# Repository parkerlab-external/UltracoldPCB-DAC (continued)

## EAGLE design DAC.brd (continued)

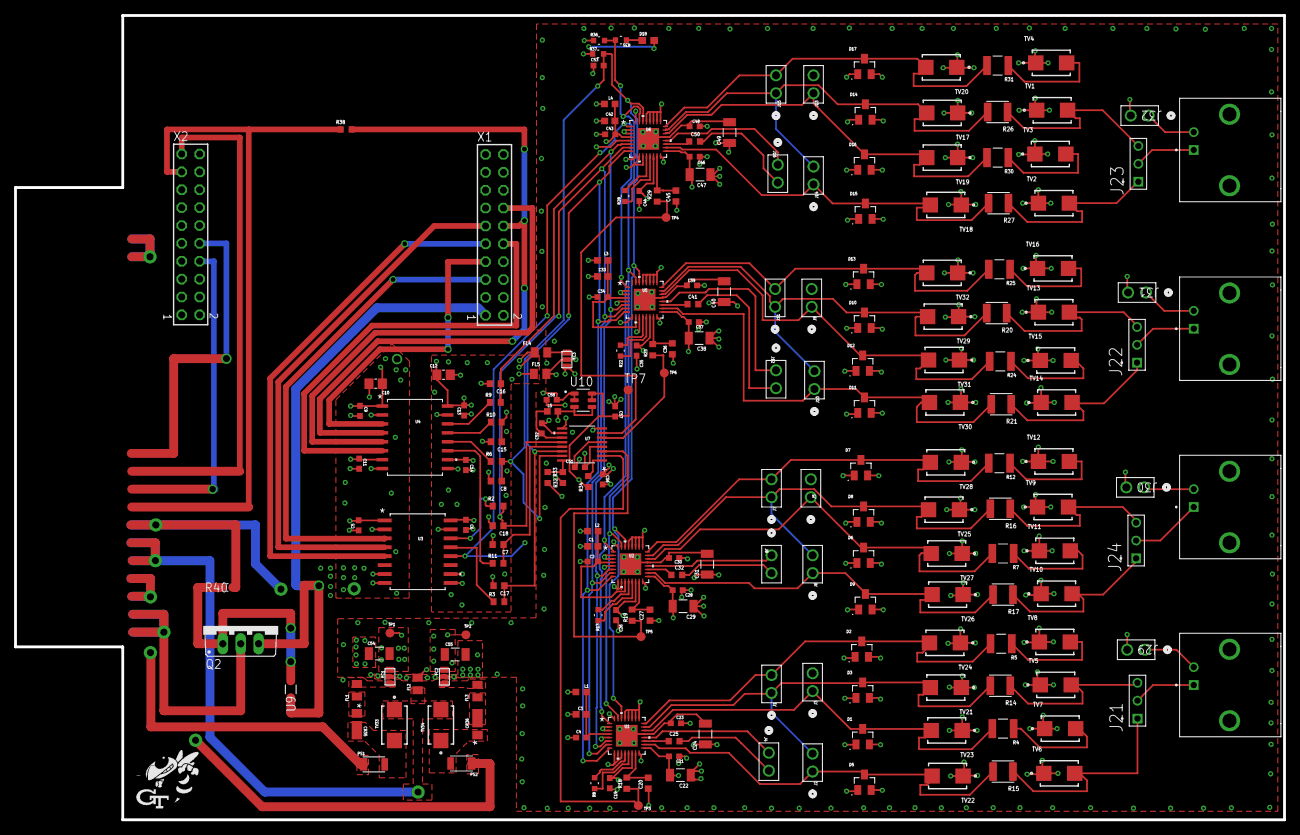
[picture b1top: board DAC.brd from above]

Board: 4 copper layers, 180.3 x 114.3 mm, 211 parts (0 on the bottom side), 116 nets.

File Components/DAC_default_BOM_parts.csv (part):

"Part","Value","Device","Package","Library","Description","AVAILABILITY","BUILT_BY","CENTERLINE_PITCH","COMMENT","COPYRIGHT","DESCRIPTION","DIGI-KEY_PART_NUMBER","EU_ROHS_COMPLIANCE","MANUFACTURER_PART_NUMBER","MF","MP","MPN","NUMBER_OF_POSITIONS","OC_FARNELL","OC_NEWARK","PACKAGE","POPULARITY","PRICE","PRODUCT_TYPE","PURCHASE-URL","SOURCELIBRARY","SOURCE_LIBRARY","TP_SIGNAL_NAME","VENDOR",
"C1","1muF 10V 0603","C0603C105K4PALTU","CAPC17595_90N_KEM","1uF-10V-0603","","","EMA_Frank","","","","","","","C0603C105K4PALTU","","","","","","","","","","","","Kemet_2020-03-25_2a","Kemet_2020-03-25_2.xlr","","Kemet",
"C2","0.1muF","GRM188R71E104KA01D","G-188_MUR","1.1uF-50V-0603","","","","","","Copyright (C) 2015 Accelerated Designs. All rights reserved","","","","GRM188R71E104KA01D","","","","","","","","","","","","Murata_2014-12-31","","","Murata",
"C3","1muF 10V 0603","C0603C105K4PALTU","CAPC17595_90N_KEM","1uF-10V-0603","","","EMA_Frank","","","","","","","C0603C105K4PALTU","","","","","","","","","","","","Kemet_2020-03-25_2a","Kemet_2020-03-25_2.xlr","","Kemet",
"C4","0.1muF","GRM188R71E104KA01D","G-188_MUR","1.1uF-50V-0603","","","","","","Copyright (C) 2015 Accelerated Designs. All rights reserved","","","","GRM188R71E104KA01D","","","","","","","","","","","","Murata_2014-12-31","","","Murata",
"C5","0.1muF","GRM188R71E104KA01D","G-188_MUR","1.1uF-50V-0603","","","","","","Copyright (C) 2015 Accelerated Designs. All rights reserved","","","","GRM188R71E104KA01D","","","","","","","","","","","","Murata_2014-12-31","","","Murata",
"C6","0.1muF","GRM188R71E104KA01D","G-188_MUR","1.1uF-50V-0603","","","","","","Copyright (C) 2015 Accelerated Designs. All rights reserved","","","","GRM188R71E104KA01D","","","","","","","","","","","","Murata_2014-12-31","","","Murata",
"C7","100pF 50V 0603","06035A101JAT2A","CAPC1608X90N","100pf_0603_capacitors","Capacitor: ceramic; MLCC; 100pF; 50V; C0G; ±5%; SMD; 0603","","","","",""," 100pF ±5% 50V Ceramic Capacitor C0G, NP0 0603 (1608 Metric) ","478-1175-1-ND","","","AVX","06035A101JAT2A","","","","","1608 AVX","","","","https://pricing.snapeda.com/search/part/06035A101JAT2A/?ref=eda","","","","",
"C8","100pF 50V 0603","06035A101JAT2A","CAPC1608X90N","100pf_0603_capacitors","Capacitor: ceramic; MLCC; 100pF; 50V; C0G; ±5%; SMD; 0603","","","","",""," 100pF ±5% 50V Ceramic Capacitor C0G, NP0 0603 (1608 Metric) ","478-1175-1-ND","","","AVX","06035A101JAT2A","","","","","1608 AVX","","","","https://pricing.snapeda.com/search/part/06035A101JAT2A/?ref=eda","","","","",
"C9","0.1muF","GRM188R71E104KA01D","G-188_MUR","1.1uF-50V-0603","","","","","","Copyright (C) 2015 Accelerated Designs. All rights reserved","","","","GRM188R71E104KA01D","","","","","","","","","","","","Murata_2014-12-31","","","Murata",
"C10","10muF","GRM21BR61A106KE14L","CAPC2012X135N","0805_10uf_capacitors","CAP 10UF 10VDC X5R 10% SMD 0805 EMBOSSED TAPE","","","","",""," SMD Capacitor X5R(EIA) with Capacitance: 10uF Tol. 10%. Rated Voltage: 10Vdc ","GRM21BR61A106KE14L-ND","","","Murata Electronics","GRM21BR61A106KE14L","","","","","0805 Murata","","","","","","","","",
"C11","0.1muF","GRM188R71E104KA01D","G-188_MUR","1.1uF-50V-0603","","","","","","Copyright (C) 2015 Accelerated Designs. All rights reserved","","","","GRM188R71E104KA01D","","","","","","","","","","","","Murata_2014-12-31","","","Murata",
"C12","10muF","GRM21BR61A106KE14L","CAPC2012X135N","0805_10uf_capacitors","CAP 10UF 10VDC X5R 10% SMD 0805 EMBOSSED TAPE","","","","",""," SMD Capacitor X5R(EIA) with Capacitance: 10uF Tol. 10%. Rated Voltage: 10Vdc ","GRM21BR61A106KE14L-ND","","","Murata Electronics","GRM21BR61A106KE14L","","","","","0805 Murata","","","","","","","","",
"C13","0.1muF","GRM188R71E104KA01D","G-188_MUR","1.1uF-50V-0603","","","","","","Copyright (C) 2015 Accelerated Designs. All rights reserved","","","","GRM188R71E104KA01D","","","","","","","","","","","","Murata_2014-12-31","","","Murata",
"C14","0.1muF","GRM188R71E104KA01D","G-188_MUR","1.1uF-50V-0603","","","","","","Copyright (C) 2015 Accelerated Designs. All rights reserved","","","","GRM188R71E104KA01D","","","","","","","","","","","","Murata_2014-12-31","","","Murata",
"C15","100pF 50V 0603","06035A101JAT2A","CAPC1608X90N","100pf_0603_capacitors","Capacitor: ceramic; MLCC; 100pF; 50V; C0G; ±5%; SMD; 0603","","","","",""," 100pF ±5% 50V Ceramic Capacitor C0G, NP0 0603 (1608 Metric) ","478-1175-1-ND","","","AVX","06035A101JAT2A","","","","","1608 AVX","","","","https://pricing.snapeda.com/search/part/06035A101JAT2A/?ref=eda","","","","",
"C16","100pF 50V 0603","06035A101JAT2A","CAPC1608X90N","100pf_0603_capacitors","Capacitor: ceramic; MLCC; 100pF; 50V; C0G; ±5%; SMD; 0603","","","","",""," 100pF ±5% 50V Ceramic Capacitor C0G, NP0 0603 (1608 Metric) ","478-1175-1-ND","","","AVX","06035A101JAT2A","","","","","1608 AVX","","","","https://pricing.snapeda.com/search/part/06035A101JAT2A/?ref=eda","","","","",
"C17","100pF 50V 0603","06035A101JAT2A","CAPC1608X90N","100pf_0603_capacitors","Capacitor: ceramic; MLCC; 100pF; 50V; C0G; ±5%; SMD; 0603","","","","",""," 100pF ±5% 50V Ceramic Capacitor C0G, NP0 0603 (1608 Metric) ","478-1175-1-ND","","","AVX","06035A101JAT2A","","","","","1608 AVX","","","","https://pricing.snapeda.com/search/part/06035A101JAT2A/?ref=eda","","","","",
"C18","100pF 50V 0603","06035A101JAT2A","CAPC1608X90N","100pf_0603_capacitors","Capacitor: ceramic; MLCC; 100pF; 50V; C0G; ±5%; SMD; 0603","","","","",""," 100pF ±5% 50V Ceramic Capacitor C0G, NP0 0603 (1608 Metric) ","478-1175-1-ND","","","AVX","06035A101JAT2A","","","","","1608 AVX","","","","https://pricing.snapeda.com/search/part/06035A101JAT2A/?ref=eda","","","","",
"C19","0.1muF","GRM188R71E104KA01D","G-188_MUR","1.1uF-50V-0603","","","","","","Copyright (C) 2015 Accelerated Designs. All rights reserved","","","","GRM188R71E104KA01D","","","","","","","","","","","","Murata_2014-12-31","","","Murata",
"C20","100pF 50V 0603","06035A101JAT2A","CAPC1608X90N","100pfcapacitor","Capacitor: ceramic; MLCC; 100pF; 50V; C0G; ±5%; SMD; 0603","","","","",""," 100pF ±5% 50V Ceramic Capacitor C0G, NP0 0603 (1608 Metric) ","478-1175-1-ND","","","AVX","06035A101JAT2A","","","","","1608 AVX","","","","https://pricing.snapeda.com/search/part/06035A101JAT2A/?ref=eda","","","","",
"C21","0.1muF","GRM188R71E104KA01D","G-188_MUR","1.1uF-50V-0603","","","","","","Copyright (C) 2015 Accelerated Designs. All rights reserved","","","","GRM188R71E104KA01D","","","","","","","","","","","","Murata_2014-12-31","","","Murata",
"C22","10muF 25V 1206","C1206C106Z3VAC7800","CAPC3216X180N","10mufcapacitors","","","","","",""," 10µF -20%, +80% 25V Ceramic Capacitor Y5V (F) 1206 (3216 Metric) ","399-15076-1-ND","","","KEMET","C1206C106Z3VAC7800","","","","","3216 KEMET","","","","https://pricing.snapeda.com/search/part/C1206C106Z3VAC7800/?ref=eda","","","","",
"C23","0.1muF","GRM188R71E104KA01D","G-188_MUR","1.1uF-50V-0603","","","","","","Copyright (C) 2015 Accelerated Designs. All rights reserved","","","","GRM188R71E104KA01D","","","","","","","","","","","","Murata_2014-12-31","","","Murata",
"C24","10muF 25V 1206","C1206C106Z3VAC7800","CAPC3216X180N","10mufcapacitors","","","","","",""," 10µF -20%, +80% 25V Ceramic Capacitor Y5V (F) 1206 (3216 Metric) ","399-15076-1-ND","","","KEMET","C1206C106Z3VAC7800","","","","","3216 KEMET","","","","https://pricing.snapeda.com/search/part/C1206C106Z3VAC7800/?ref=eda","","","","",
"C25","1nF 50V 0603","GRM1885C1H102JA01D","CAPC1608X90N","1nfcapacitor","","","","","",""," SMD Capacitor C0G(EIA) with Capacitance: 1000pF Tol. 5%. Rated Voltage: 50Vdc ","490-1451-1-ND","","","Murata","GRM1885C1H102JA01D","","","","","1608 Murata","","","","https://pricing.snapeda.com/search/part/GRM1885C1H102JA01D/?ref=eda","","","","",
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
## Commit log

2025-03-03 Design files.
